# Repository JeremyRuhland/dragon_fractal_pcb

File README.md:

FR-4 Lightpipe Experiment #1
============================

Conbadges and user interfaces occasionally use FR-4 as a light diffuser with downward facing LEDs or a secondary PCB. In this experiment I will attempt to install LEDs internally within a single PCB and release diffused light through surface features.

The basic concept is to insert LEDs vertically through non-plated holes. Solder will connect the component leads to exposed copper annulars on the front and back side of the board and retain the component inside the hole. 0603 parts are just slightly shorter than a standard 1.6mm PCB and a 0.8mm tall LED fits snugly into a 1.1mm hole. LEDs are positioned facing inward.

Light is confined within the FR-4 substrate with copper pours and a via fence around the outer edge of the board. The reflective underside of the copper will redirect light toward the center of the PCB. Holes in the front copper pour and soldermask allow light to exit the board.

Power is supplied to the board using a PCB USB-A plug. Two layers of electrical tape are applied to the underside of the plug to bring the 1.6mm PCB to a standard USB plug thickness of 2.2mm.

Fabrication
-----------

I went with JLCPCB to fabricate these boards and was very happy with the quality. I emailed them beforehand to ask about how they wanted me to notate NPTHs that went through copper pours (usually this signals a PTH). In the end I added a build note to my documentation gerber which called out the drill diagram and I exported two different excellon files, one for NPTH and another for PTH. I also noted this as a comment on the online order form.

They also honored my request to place order number codes on the back side of the board to keep the front pretty. Due to process limitations they weren't able to drill directly through the copper like I wanted but they added a very small pullback to the annular and drilled through the exposed FR-4 which didn't present any problem for assembly. In the future it would probably be easier to modify my library component to present this part as a standard NPTH surrounded (but not touched by) a ring of exposed copper to preclude the need for all these notes.

Findings
--------

See [Hackaday.io page](https://hackaday.io/project/167113-fr-4-lightpipe-experiment-1) for photographs.

Assembly of the board was straightforward. LEDs fit easily into their holes as long as they were aligned normal to the surface. Friction was sufficient to hold them in place before soldering, even if the board was lifted.

Care had to be taken while soldering to ensure the solder successfully made contact with the component leads and did not simply dome over it. Diagnosis can be performed with a multimeter in diode mode. Connection to ground pours was difficult despite thermals but it worked well once the copper heated a bit. I cannot recommend using additional flux for these components as the off-gassing causes the cavity to pressurize while the final solder cap is cooling and it will pop like a bubble.

This rev of the board did not perform as expected. Although the via wall appeared to successfully redirect the majority of the light into the FR-4, illumination only occurred within 15mm of the LEDs.

As a test I pressed a powerful external light to the front surface of the board but was unable to see any light emerging through the empty NPTHs. I also removed a portion of the bottom copper pour using sandpaper to [observe the translucency](https://video.twimg.com/ext_tw_video/1154599657135149056/pu/vid/720x1280/HLElvOXAGY346I9b.mp4) (mp4). In another test I installed the LEDs facing outwards to judge how effective the via fence was.

Conclusion
----------

FR-4 apparently absorbs a lot more light that I thought. It doesn't seem like all that much when an LED only has to go through 1.6mm of it but in my tests 15mm was the limit of transmission with the aid of the copper pours. I estimate each LED was putting out a third of a lumen, so the entire board had about 2.6.

Fiberglass is an anisotropic material but I'm not sure how its optical properties change with orientation to the weave. Would light travel any better front-to-back through a PCB 10x as thick? It seems like the glass fiber would absorb less light than the epoxy since glass is kinda known for its transparency but there's a lot more scattering surfaces parallel to the fibers so light transmission might be worse in this orientation. Transmissive properties may differ with wavelength as well.

In a future rev I would like to try cramming an unreasonable amount of LEDs into the board but I think this method of illumination is a dead end. The ultimate limit is the thermal dissipation possible with 0603 LEDs that are buried inside FR-4. Larger (and brighter) packages will not fit within the 1.6mm PCB.

The oreo construction method might prove useful for other projects and should be explored further.

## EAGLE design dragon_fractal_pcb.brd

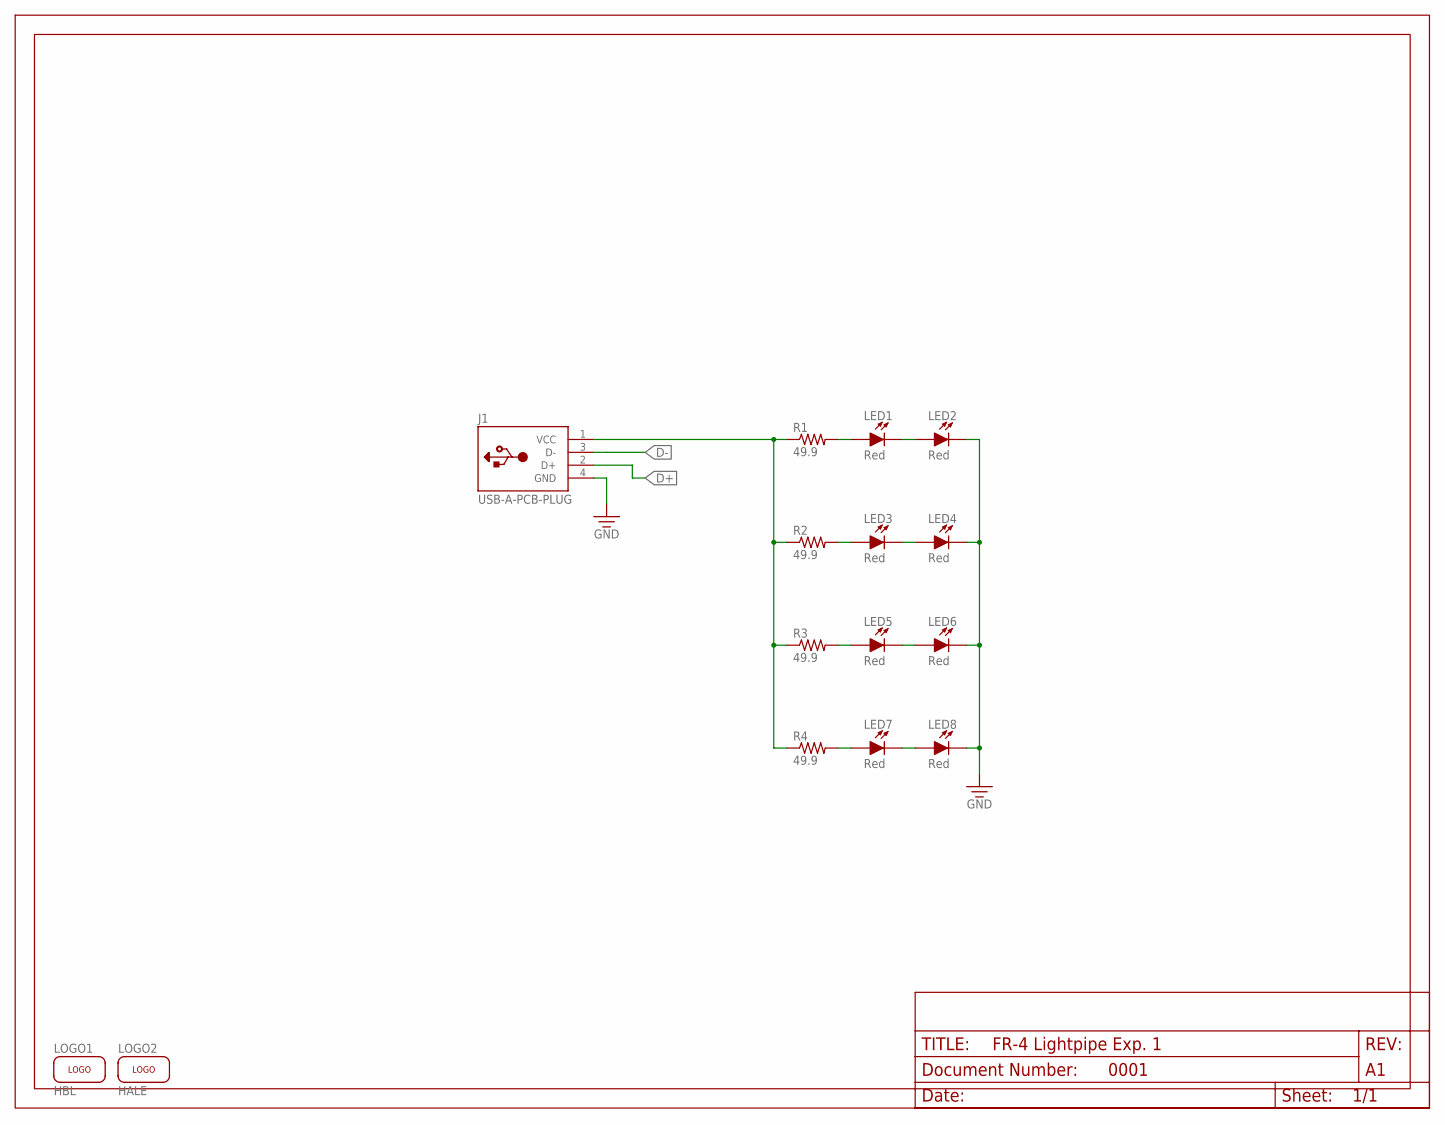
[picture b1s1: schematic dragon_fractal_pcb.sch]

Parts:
J1: USB-A-PCB-PLUG; USB-A-PLUG-PCB
LED1, LED2, LED3, LED4, LED5, LED6, LED7, LED8: Red; LED-TH-OREO; DIGIKEY 160-1436-1-ND
LOGO1: HBL; HACKERBOT-SILK-ICON
LOGO2: HALE; HALE-SILK-ICON
R1, R2, R3, R4: 49.9; 0603-NONPOLAR; DIGIKEY P49.9HCT-ND
U$1: FRAME-8.5X11-LANDSCAPE-LET; FRAME-8.5X11-LANDSCAPE

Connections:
D+: J1.2 (D+)
D-: J1.3 (D-)
GND: J1.4 (GND), LED2.C (C1), LED4.C (C1), LED6.C (C1), LED8.C (C1)
unnamed: J1.1 (VCC), R1.1, R2.1, R3.1, R4.1
unnamed: LED1.C (C1), LED2.A (A1)
unnamed: LED3.C (C1), LED4.A (A1)
unnamed: LED5.C (C1), LED6.A (A1)
unnamed: LED7.C (C1), LED8.A (A1)
unnamed: LED7.A (A1), R4.2
unnamed: LED5.A (A1), R3.2
unnamed: LED3.A (A1), R2.2
unnamed: LED1.A (A1), R1.2

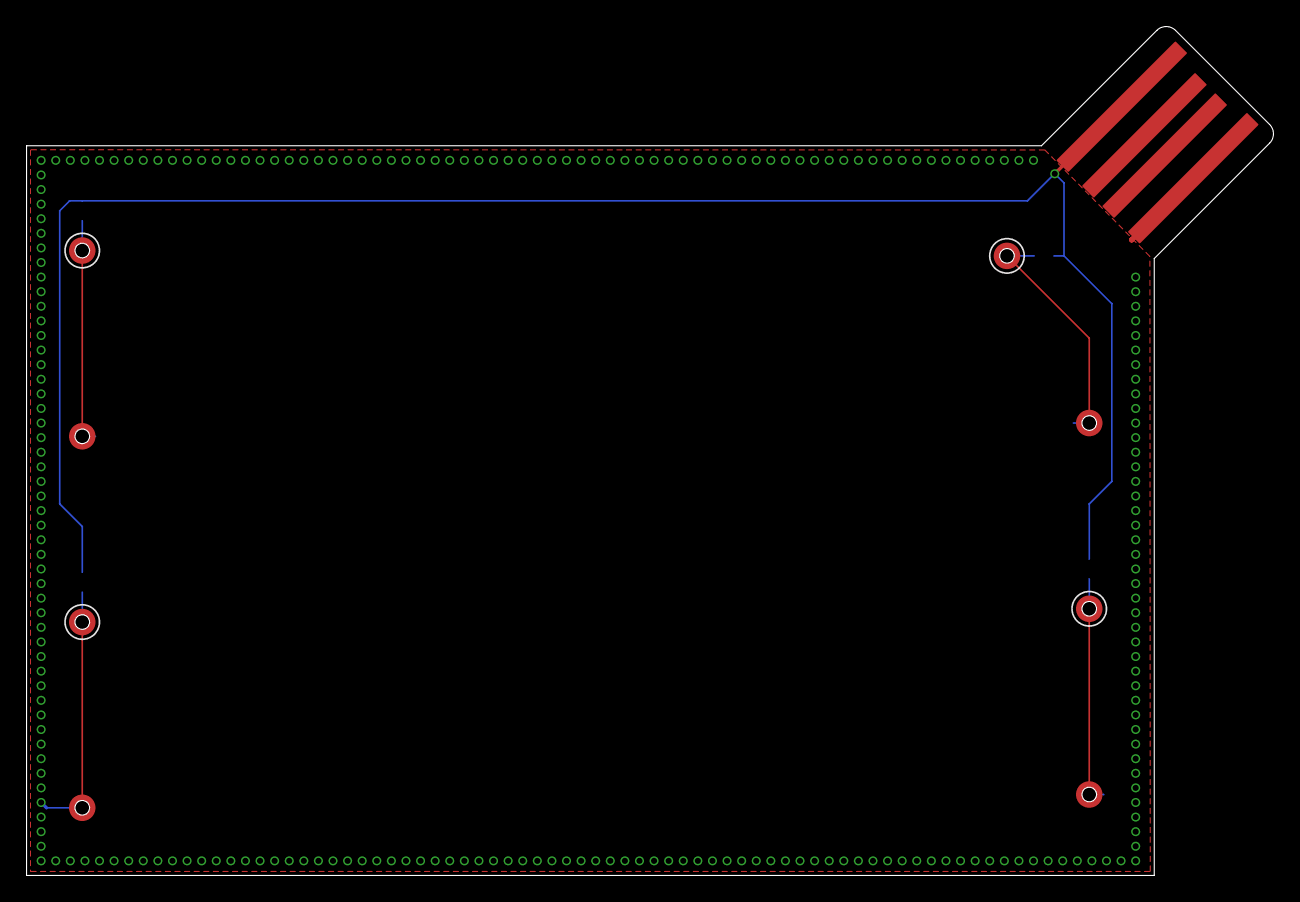
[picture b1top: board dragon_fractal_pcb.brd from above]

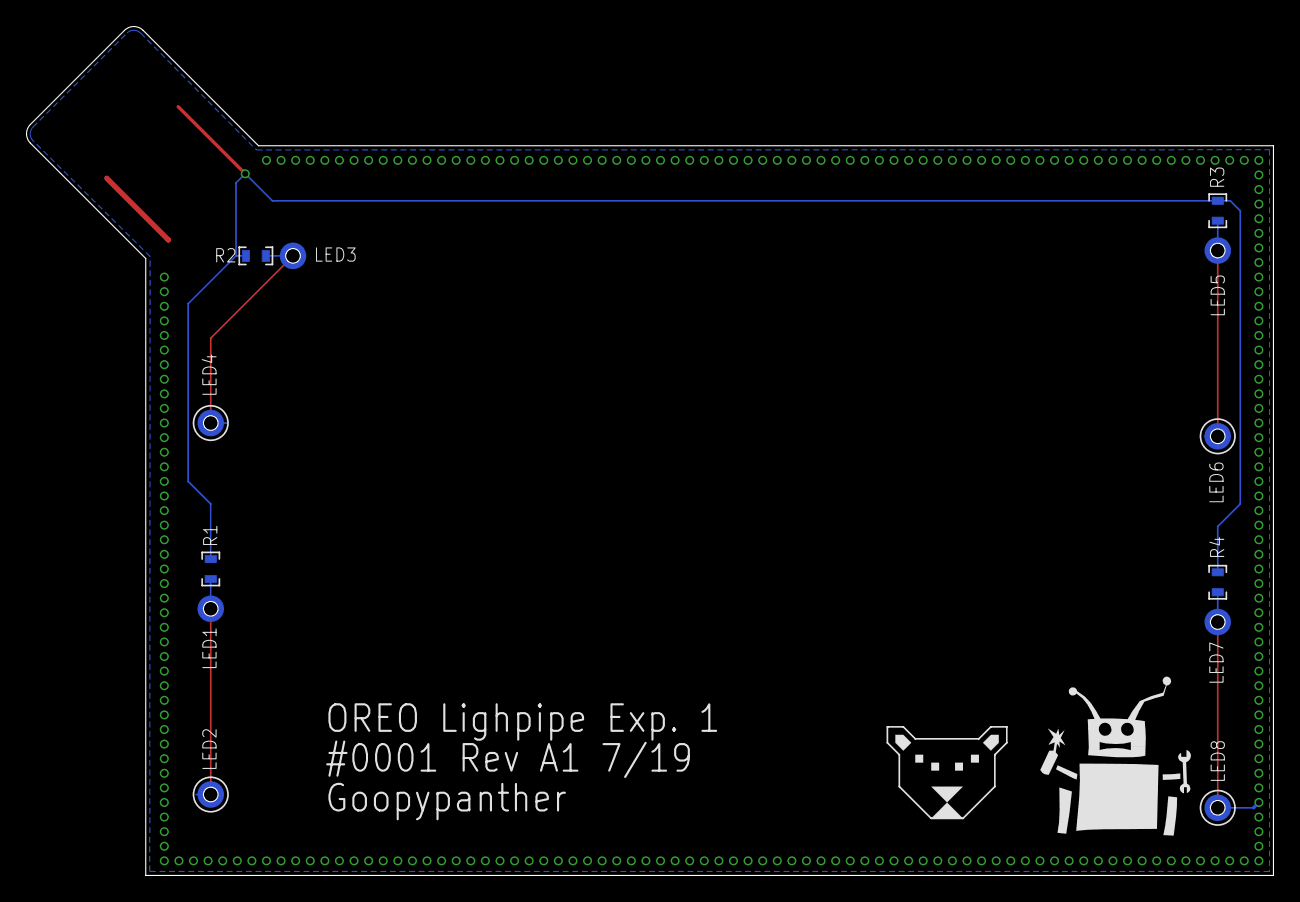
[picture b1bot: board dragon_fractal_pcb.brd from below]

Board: 2 copper layers, 94.0 x 64.0 mm, 17 parts (10 on the bottom side), 10 nets.

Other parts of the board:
DRILEGEND: DRILEGEND

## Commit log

2019-08-13 Inital
2019-08-13 Added readme
